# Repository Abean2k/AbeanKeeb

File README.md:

# AbeanKeeb
A 65 percent custom layout, tactile keyboard

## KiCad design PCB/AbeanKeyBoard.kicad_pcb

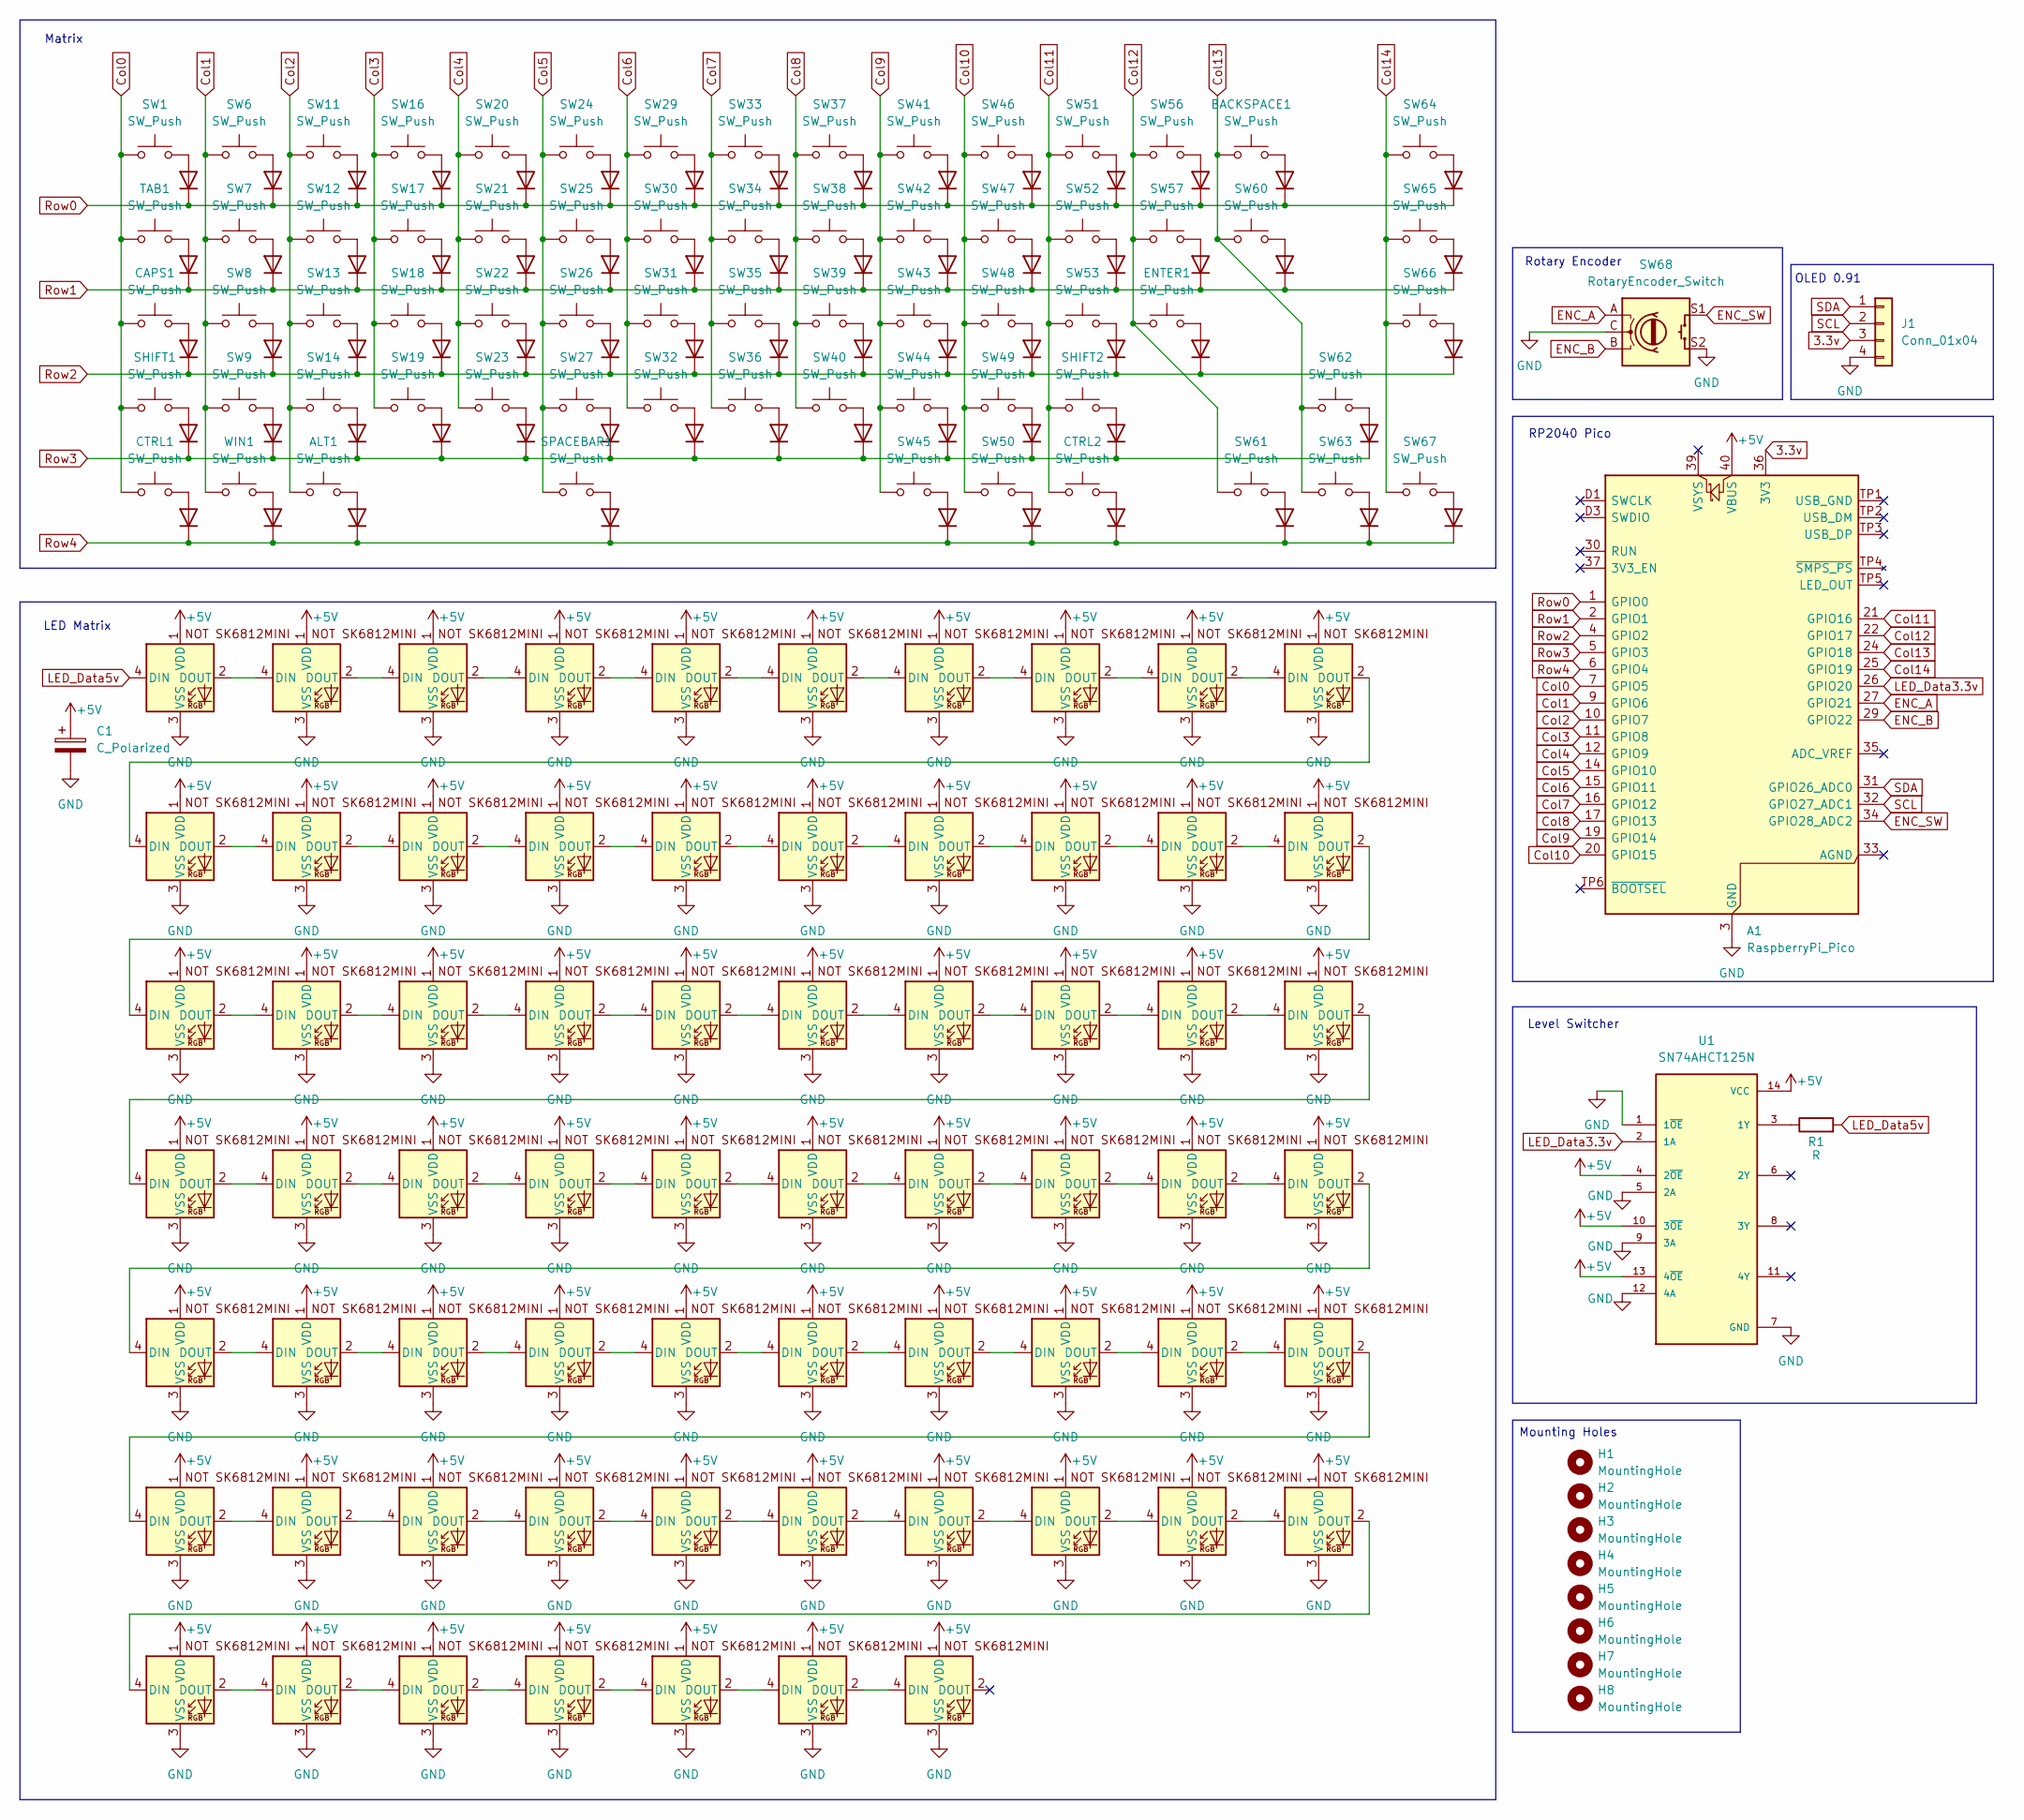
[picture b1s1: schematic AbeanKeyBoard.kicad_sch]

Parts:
A1: RaspberryPi_Pico; RaspberryPi_Pico_SMD
ALT1: SW_Push; SW_Cherry_MX_1.25u_PCB
BACKSPACE1: SW_Push; SW_Cherry_MX_2.00u_PCB
C1: C_Polarized; CP_Elec_6.3x5.4
CAPS1: SW_Push; SW_Cherry_MX_1.75u_PCB
CTRL1, CTRL2: SW_Push; SW_Cherry_MX_1.25u_PCB
D1, D2, D3, D4, D5, D6, D7, D18, D19, D20, D21, D22, D23, D24, D30, D31, D32, D33, D34, D35, D36, D45, D46, D47, D48, D49, D50, D51, D57, D58, D59, D60, D61, D62, D63, D72, D73, D74, D75, D76, D77, D78, D83, D84, D85, D86, D87, D88, D89, D100, D101, D102, D103, D104, D105, D111, D112, D113, D114, D115, D116, D123, D124, D125, D126, D127, D128: SK6812MINI-E; SK6812MINI-E_fixed
D8, D9, D10, D11, D12, D13, D14, D15, D16, D17, D25, D26, D27, D28, D29, D37, D38, D39, D40, D41, D42, D43, D44, D52, D53, D54, D55, D56, D64, D65, D66, D67, D68, D69, D70, D71, D79, D80, D81, D82, D90, D91, D92, D93, D94, D95, D96, D97, D98, D99, D106, D107, D108, D109, D110, D117, D118, D119, D120, D121, D122, D129, D130, D131, D132, D133, D134: 1N4148; D_DO-35_SOD27_P7.62mm_Horizontal
ENTER1: SW_Push; SW_Cherry_MX_2.25u_PCB
H1, H2, H3, H4, H5, H6, H7, H8: MountingHole; MountingHole_4.3mm_M4
J1: Conn_01x04; PinHeader_1x04_P2.54mm_Vertical
R1: R; R_1206_3216Metric_Pad1.30x1.75mm_HandSolder
SHIFT1: SW_Push; SW_Cherry_MX_2.25u_PCB
SHIFT2: SW_Push; SW_Cherry_MX_2.00u_PCB
SPACEBAR1: SW_Push; SW_Cherry_MX_6.25u_PCB
SW1, SW6, SW7, SW8, SW9, SW11, SW12, SW13, SW14, SW16, SW17, SW18, SW19, SW20, SW21, SW22, SW23, SW24, SW25, SW26, SW27, SW29, SW30, SW31, SW32, SW33, SW34, SW35, SW36, SW37, SW38, SW39, SW40, SW41, SW42, SW43, SW44, SW45, SW46, SW47, SW48, SW49, SW50, SW51, SW52, SW53, SW56, SW57, SW60, SW61, SW62, SW63, SW64, SW65, SW66, SW67: SW_Push; SW_Cherry_MX_1.00u_PCB
SW68: RotaryEncoder_Switch; RotaryEncoder_Alps_EC11E-Switch_Vertical_H20mm
TAB1: SW_Push; SW_Cherry_MX_1.50u_PCB
U1: SN74AHCT125N; SOIC-14_3.9x8.7mm_P1.27mm; PARTREV Q
WIN1: SW_Push; SW_Cherry_MX_1.25u_PCB

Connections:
3.3v: A1.36 (3V3), J1.3
+5V: A1.40 (VBUS), C1.1, D1.1 (VDD), D2.1 (VDD), D3.1 (VDD), D4.1 (VDD), D5.1 (VDD), D6.1 (VDD), D7.1 (VDD), D18.1 (VDD), D19.1 (VDD), D20.1 (VDD), D21.1 (VDD), D22.1 (VDD), D23.1 (VDD), D24.1 (VDD), D30.1 (VDD), D31.1 (VDD), D32.1 (VDD), D33.1 (VDD), D34.1 (VDD), D35.1 (VDD), D36.1 (VDD), D45.1 (VDD), D46.1 (VDD), D47.1 (VDD), D48.1 (VDD), D49.1 (VDD), D50.1 (VDD), D51.1 (VDD), D57.1 (VDD), D58.1 (VDD), D59.1 (VDD), D60.1 (VDD), D61.1 (VDD), D62.1 (VDD), D63.1 (VDD), D72.1 (VDD), D73.1 (VDD), D74.1 (VDD), D75.1 (VDD), D76.1 (VDD), D77.1 (VDD), D78.1 (VDD), D83.1 (VDD), D84.1 (VDD), D85.1 (VDD), D86.1 (VDD), D87.1 (VDD), D88.1 (VDD), D89.1 (VDD), D100.1 (VDD), D101.1 (VDD), D102.1 (VDD), D103.1 (VDD), D104.1 (VDD), D105.1 (VDD), D111.1 (VDD), D112.1 (VDD), D113.1 (VDD), D114.1 (VDD), D115.1 (VDD), D116.1 (VDD), D123.1 (VDD), D124.1 (VDD), D125.1 (VDD), D126.1 (VDD), D127.1 (VDD), D128.1 (VDD), U1.4 (2~OE), U1.10 (3~OE), U1.13 (4~OE), U1.14 (VCC)
Col0: A1.7 (GPIO5), CAPS1.1, CTRL1.1, SHIFT1.1, SW1.1, TAB1.1
Col1: A1.9 (GPIO6), SW6.1, SW7.1, SW8.1, SW9.1, WIN1.1
Col2: A1.10 (GPIO7), ALT1.1, SW11.1, SW12.1, SW13.1, SW14.1
Col3: A1.11 (GPIO8), SW16.1, SW17.1, SW18.1, SW19.1
Col4: A1.12 (GPIO9), SW20.1, SW21.1, SW22.1, SW23.1
Col5: A1.14 (GPIO10), SPACEBAR1.1, SW24.1, SW25.1, SW26.1, SW27.1
Col6: A1.15 (GPIO11), SW29.1, SW30.1, SW31.1, SW32.1
Col7: A1.16 (GPIO12), SW33.1, SW34.1, SW35.1, SW36.1
Col8: A1.17 (GPIO13), SW37.1, SW38.1, SW39.1, SW40.1
Col9: A1.19 (GPIO14), SW41.1, SW42.1, SW43.1, SW44.1, SW45.1
Col10: A1.20 (GPIO15), SW46.1, SW47.1, SW48.1, SW49.1, SW50.1
Col11: A1.21 (GPIO16), CTRL2.1, SHIFT2.1, SW51.1, SW52.1, SW53.1
Col12: A1.22 (GPIO17), ENTER1.1, SW56.1, SW57.1, SW61.1
Col13: A1.24 (GPIO18), BACKSPACE1.1, SW60.1, SW62.1, SW63.1
Col14: A1.25 (GPIO19), SW64.1, SW65.1, SW66.1, SW67.1
ENC_A: A1.27 (GPIO21), SW68.A
ENC_B: A1.29 (GPIO22), SW68.B
ENC_SW: A1.34 (GPIO28_ADC2), SW68.S1
GND: A1.3 (GND), A1.8 (GND), A1.13 (GND), A1.18 (GND), A1.23 (GND), A1.28 (GND), A1.38 (GND), A1.D2 (GND), C1.2, D1.3 (VSS), D2.3 (VSS), D3.3 (VSS), D4.3 (VSS), D5.3 (VSS), D6.3 (VSS), D7.3 (VSS), D18.3 (VSS), D19.3 (VSS), D20.3 (VSS), D21.3 (VSS), D22.3 (VSS), D23.3 (VSS), D24.3 (VSS), D30.3 (VSS), D31.3 (VSS), D32.3 (VSS), D33.3 (VSS), D34.3 (VSS), D35.3 (VSS), D36.3 (VSS), D45.3 (VSS), D46.3 (VSS), D47.3 (VSS), D48.3 (VSS), D49.3 (VSS), D50.3 (VSS), D51.3 (VSS), D57.3 (VSS), D58.3 (VSS), D59.3 (VSS), D60.3 (VSS), D61.3 (VSS), D62.3 (VSS), D63.3 (VSS), D72.3 (VSS), D73.3 (VSS), D74.3 (VSS), D75.3 (VSS), D76.3 (VSS), D77.3 (VSS), D78.3 (VSS), D83.3 (VSS), D84.3 (VSS), D85.3 (VSS), D86.3 (VSS), D87.3 (VSS), D88.3 (VSS), D89.3 (VSS), D100.3 (VSS), D101.3 (VSS), D102.3 (VSS), D103.3 (VSS), D104.3 (VSS), D105.3 (VSS), D111.3 (VSS), D112.3 (VSS), D113.3 (VSS), D114.3 (VSS), D115.3 (VSS), D116.3 (VSS), D123.3 (VSS), D124.3 (VSS), D125.3 (VSS), D126.3 (VSS), D127.3 (VSS), D128.3 (VSS), J1.4, SW68.C, SW68.S2, U1.1 (1~OE), U1.5 (2A), U1.7 (GND), U1.9 (3A), U1.12 (4A)
LED_Data3.3v: A1.26 (GPIO20), U1.2 (1A)
LED_Data5v: D1.4 (DIN), R1.2
unnamed: D1.2 (DOUT), D18.4 (DIN)
unnamed: D8.2 (A), SW1.2
unnamed: D9.2 (A), TAB1.2
unnamed: CAPS1.2, D10.2 (A)
unnamed: D11.2 (A), SHIFT1.2
unnamed: CTRL1.2, D12.2 (A)
unnamed: D13.2 (A), SW6.2
unnamed: D14.2 (A), SW7.2
unnamed: D15.2 (A), SW8.2
unnamed: D16.2 (A), SW9.2
unnamed: D17.2 (A), WIN1.2
unnamed: D18.2 (DOUT), D30.4 (DIN)
unnamed: D2.2 (DOUT), D19.4 (DIN)
unnamed: D19.2 (DOUT), D31.4 (DIN)
unnamed: D3.2 (DOUT), D20.4 (DIN)
unnamed: D20.2 (DOUT), D32.4 (DIN)
unnamed: D4.2 (DOUT), D21.4 (DIN)
unnamed: D21.2 (DOUT), D33.4 (DIN)
unnamed: D5.2 (DOUT), D22.4 (DIN)
unnamed: D22.2 (DOUT), D34.4 (DIN)
unnamed: D6.2 (DOUT), D23.4 (DIN)
unnamed: D23.2 (DOUT), D35.4 (DIN)
unnamed: D7.2 (DOUT), D24.4 (DIN)
unnamed: D24.2 (DOUT), D36.4 (DIN)
unnamed: D25.2 (A), SW11.2
unnamed: D26.2 (A), SW12.2
unnamed: D27.2 (A), SW13.2
unnamed: D28.2 (A), SW14.2
unnamed: ALT1.2, D29.2 (A)
unnamed: D30.2 (DOUT), D45.4 (DIN)
unnamed: D31.2 (DOUT), D46.4 (DIN)
unnamed: D32.2 (DOUT), D47.4 (DIN)
unnamed: D33.2 (DOUT), D48.4 (DIN)
unnamed: D34.2 (DOUT), D49.4 (DIN)
unnamed: D35.2 (DOUT), D50.4 (DIN)
unnamed: D36.2 (DOUT), D51.4 (DIN)
unnamed: D37.2 (A), SW16.2
unnamed: D38.2 (A), SW17.2
unnamed: D39.2 (A), SW18.2
unnamed: D40.2 (A), SW19.2
unnamed: D41.2 (A), SW20.2
unnamed: D42.2 (A), SW21.2
unnamed: D43.2 (A), SW22.2
unnamed: D44.2 (A), SW23.2
unnamed: D45.2 (DOUT), D57.4 (DIN)
unnamed: D46.2 (DOUT), D58.4 (DIN)
unnamed: D47.2 (DOUT), D59.4 (DIN)
unnamed: D48.2 (DOUT), D60.4 (DIN)
unnamed: D49.2 (DOUT), D61.4 (DIN)
unnamed: D50.2 (DOUT), D62.4 (DIN)
unnamed: D51.2 (DOUT), D63.4 (DIN)
unnamed: D52.2 (A), SW24.2
unnamed: D53.2 (A), SW25.2
unnamed: D54.2 (A), SW26.2
unnamed: D55.2 (A), SW27.2
unnamed: D56.2 (A), SPACEBAR1.2
unnamed: D57.2 (DOUT), D72.4 (DIN)
unnamed: D58.2 (DOUT), D73.4 (DIN)
unnamed: D59.2 (DOUT), D74.4 (DIN)
unnamed: D60.2 (DOUT), D75.4 (DIN)
unnamed: D61.2 (DOUT), D76.4 (DIN)
unnamed: D62.2 (DOUT), D77.4 (DIN)
unnamed: D63.2 (DOUT), D78.4 (DIN)
unnamed: D64.2 (A), SW29.2
unnamed: D65.2 (A), SW30.2
unnamed: D66.2 (A), SW31.2
unnamed: D67.2 (A), SW32.2
unnamed: D68.2 (A), SW33.2
unnamed: D69.2 (A), SW34.2
unnamed: D70.2 (A), SW35.2
unnamed: D71.2 (A), SW36.2
unnamed: D72.2 (DOUT), D83.4 (DIN)
unnamed: D73.2 (DOUT), D84.4 (DIN)
unnamed: D74.2 (DOUT), D85.4 (DIN)
unnamed: D75.2 (DOUT), D86.4 (DIN)
unnamed: D76.2 (DOUT), D87.4 (DIN)
unnamed: D77.2 (DOUT), D88.4 (DIN)
unnamed: D78.2 (DOUT), D89.4 (DIN)
unnamed: D79.2 (A), SW37.2
unnamed: D80.2 (A), SW38.2
unnamed: D81.2 (A), SW39.2
unnamed: D82.2 (A), SW40.2
unnamed: D90.2 (A), SW41.2
unnamed: D91.2 (A), SW42.2
unnamed: D92.2 (A), SW43.2
unnamed: D93.2 (A), SW44.2
unnamed: D94.2 (A), SW45.2
unnamed: D95.2 (A), SW46.2
unnamed: D96.2 (A), SW47.2
unnamed: D97.2 (A), SW48.2
unnamed: D98.2 (A), SW49.2
unnamed: D99.2 (A), SW50.2
unnamed: D83.2 (DOUT), D100.4 (DIN)
unnamed: D100.2 (DOUT), D111.4 (DIN)
unnamed: D84.2 (DOUT), D101.4 (DIN)
unnamed: D101.2 (DOUT), D112.4 (DIN)
unnamed: D85.2 (DOUT), D102.4 (DIN)
unnamed: D102.2 (DOUT), D113.4 (DIN)
unnamed: D86.2 (DOUT), D103.4 (DIN)
unnamed: D103.2 (DOUT), D114.4 (DIN)
unnamed: D87.2 (DOUT), D104.4 (DIN)
unnamed: D104.2 (DOUT), D115.4 (DIN)
unnamed: D88.2 (DOUT), D105.4 (DIN)
unnamed: D105.2 (DOUT), D116.4 (DIN)
unnamed: D106.2 (A), SW51.2
unnamed: D107.2 (A), SW52.2
unnamed: D108.2 (A), SW53.2
unnamed: D109.2 (A), SHIFT2.2
unnamed: CTRL2.2, D110.2 (A)
unnamed: D111.2 (DOUT), D123.4 (DIN)
unnamed: D112.2 (DOUT), D124.4 (DIN)
unnamed: D113.2 (DOUT), D125.4 (DIN)
unnamed: D114.2 (DOUT), D126.4 (DIN)
unnamed: D115.2 (DOUT), D127.4 (DIN)
unnamed: D116.2 (DOUT), D128.4 (DIN)
unnamed: D117.2 (A), SW56.2
unnamed: D118.2 (A), SW57.2
unnamed: D119.2 (A), ENTER1.2
unnamed: BACKSPACE1.2, D120.2 (A)
unnamed: D121.2 (A), SW60.2
unnamed: D122.2 (A), SW61.2
unnamed: D2.4 (DIN), D123.2 (DOUT)
unnamed: D3.4 (DIN), D124.2 (DOUT)
unnamed: D4.4 (DIN), D125.2 (DOUT)
unnamed: D5.4 (DIN), D126.2 (DOUT)
unnamed: D6.4 (DIN), D127.2 (DOUT)
unnamed: D7.4 (DIN), D128.2 (DOUT)
unnamed: D129.2 (A), SW62.2
unnamed: D130.2 (A), SW63.2
unnamed: D131.2 (A), SW64.2
unnamed: D132.2 (A), SW65.2
unnamed: D133.2 (A), SW66.2
unnamed: D134.2 (A), SW67.2
unnamed: R1.1, U1.3 (1Y)
Row0: A1.1 (GPIO0), D8.1 (K), D13.1 (K), D25.1 (K), D37.1 (K), D41.1 (K), D52.1 (K), D64.1 (K), D68.1 (K), D79.1 (K), D90.1 (K), D95.1 (K), D106.1 (K), D117.1 (K), D120.1 (K), D131.1 (K)
Row1: A1.2 (GPIO1), D9.1 (K), D14.1 (K), D26.1 (K), D38.1 (K), D42.1 (K), D53.1 (K), D65.1 (K), D69.1 (K), D80.1 (K), D91.1 (K), D96.1 (K), D107.1 (K), D118.1 (K), D121.1 (K), D132.1 (K)
Row2: A1.4 (GPIO2), D10.1 (K), D15.1 (K), D27.1 (K), D39.1 (K), D43.1 (K), D54.1 (K), D66.1 (K), D70.1 (K), D81.1 (K), D92.1 (K), D97.1 (K), D108.1 (K), D119.1 (K), D133.1 (K)
Row3: A1.5 (GPIO3), D11.1 (K), D16.1 (K), D28.1 (K), D40.1 (K), D44.1 (K), D55.1 (K), D67.1 (K), D71.1 (K), D82.1 (K), D93.1 (K), D98.1 (K), D109.1 (K), D129.1 (K)
Row4: A1.6 (GPIO4), D12.1 (K), D17.1 (K), D29.1 (K), D56.1 (K), D94.1 (K), D99.1 (K), D110.1 (K), D122.1 (K), D130.1 (K), D134.1 (K)
SCL: A1.32 (GPIO27_ADC1), J1.2
SDA: A1.31 (GPIO26_ADC0), J1.1

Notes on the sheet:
Rotary Encoder
Mounting Holes
Matrix
OLED 0.91
LED Matrix
Level Switcher
RP2040 Pico

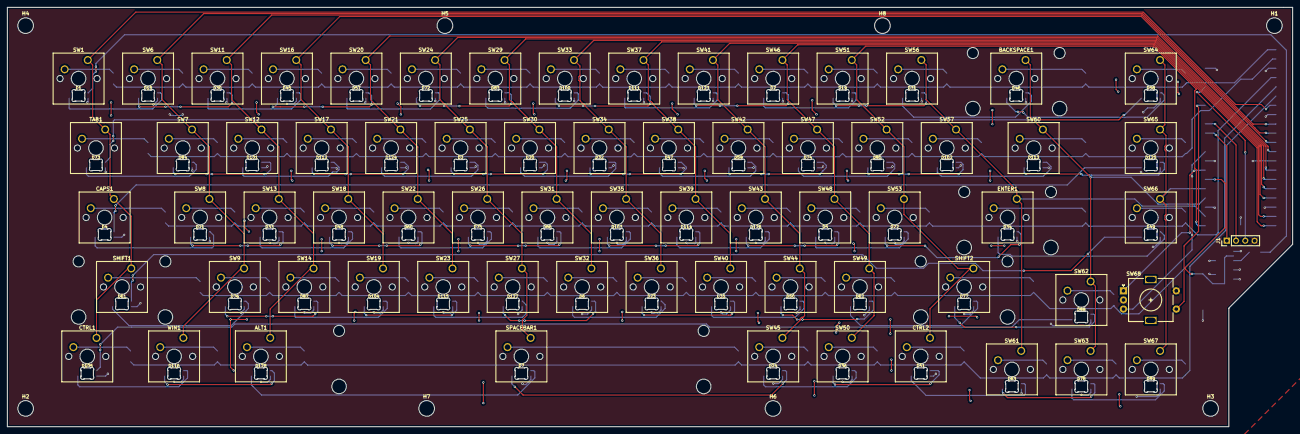
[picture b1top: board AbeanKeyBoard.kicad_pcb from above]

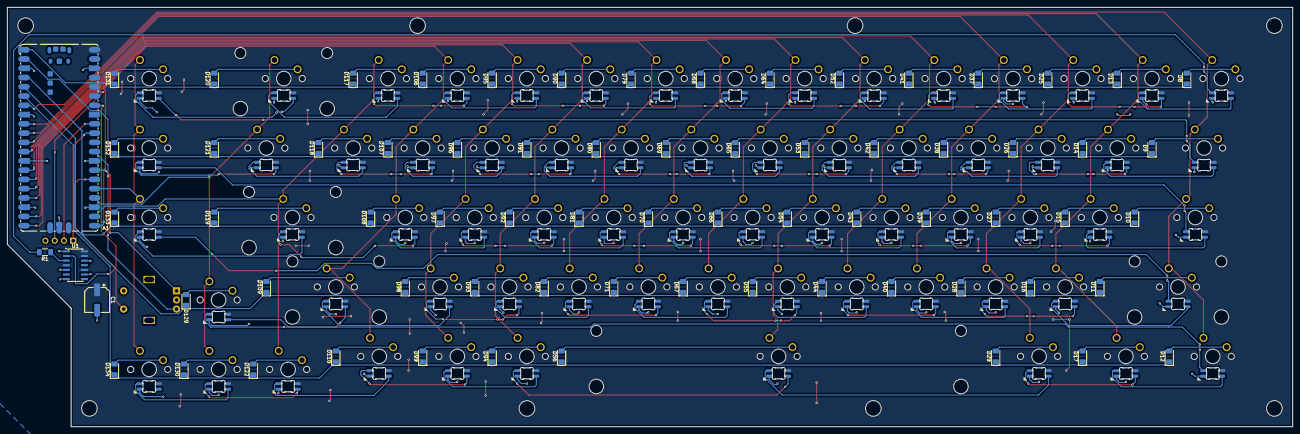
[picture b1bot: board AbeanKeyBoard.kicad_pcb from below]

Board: 2 copper layers, 352.5 x 115.0 mm, 215 parts (71 on the bottom side), 164 nets.

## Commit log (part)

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2026-06-19 PCB Upload
